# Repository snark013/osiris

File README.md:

# Osiris

65%/75% size (68/78 keys) mechanical keyboard with optional functions keys section.
Osiris can use any supported controller in Pro Micro form factor ([Alvaro](https://github.com/Ariamelon/Alvaro) and [nRFMicro](https://github.com/joric/nrfmicro/wiki) controllers recommended).

Keyboards  photo -

Bluetooth connected (nRFMicro) 78 keys keyboard

USB connected (Pro Micro) 68 keys keyboard with RGB backlight

First prototype (USB connected, Pro Micro) 78 keys keyboard

KiCAD images -

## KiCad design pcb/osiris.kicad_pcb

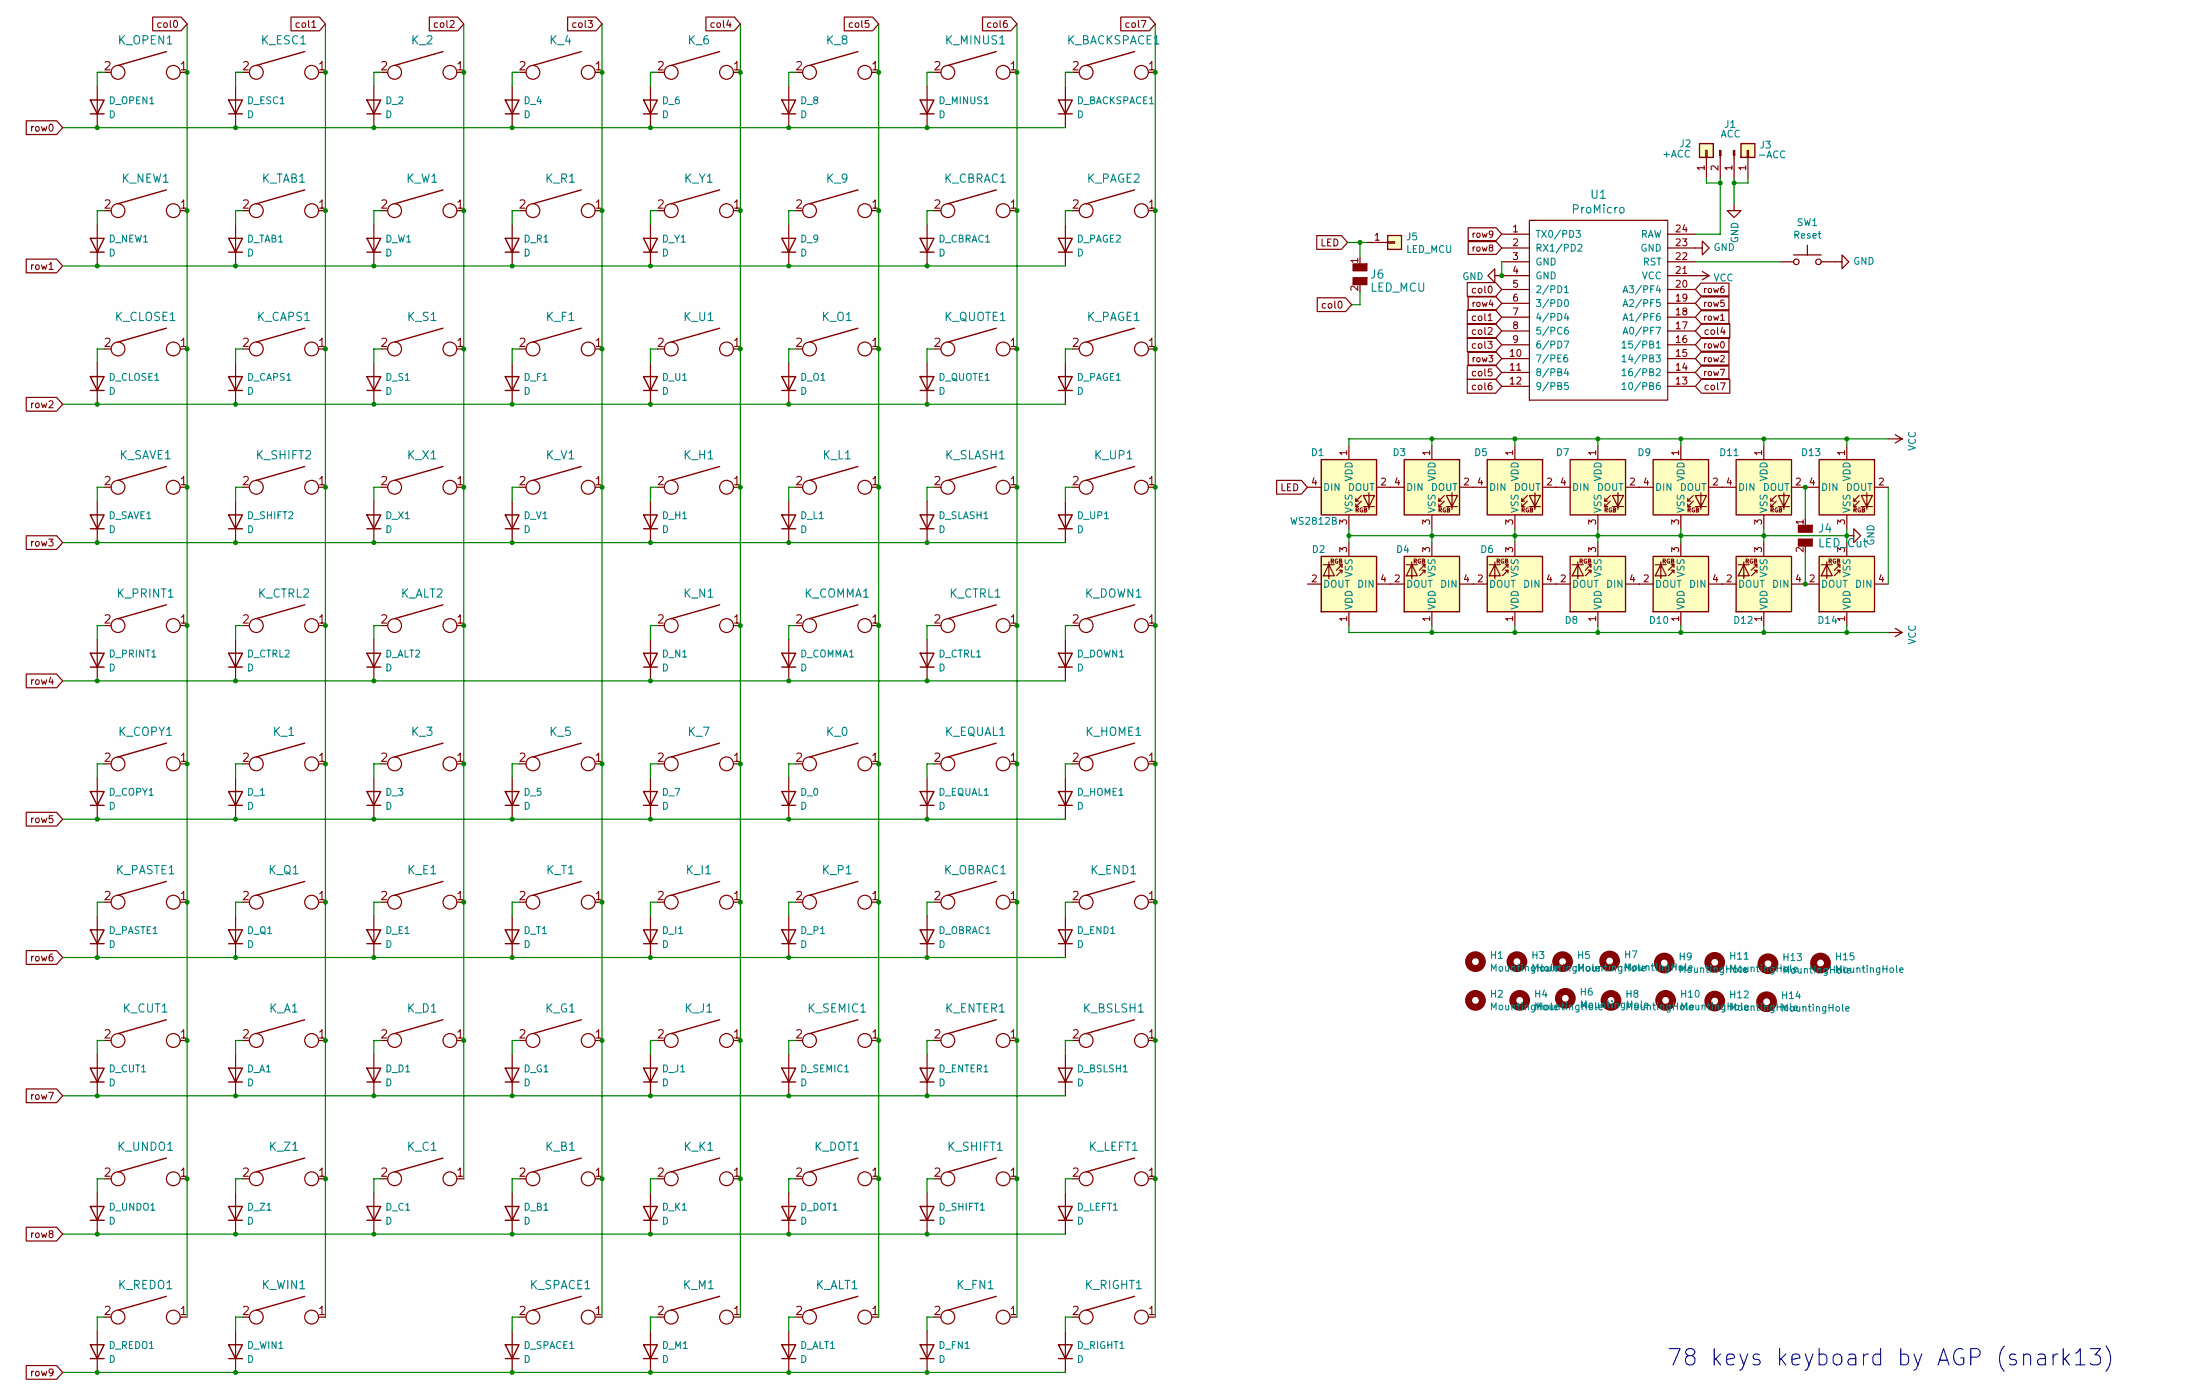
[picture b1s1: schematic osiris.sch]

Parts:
D1, D2, D3, D4, D5, D6, D7, D8, D9, D10, D11, D12, D13, D14: WS2812B; LED_WS2812B_PLCC4_5.0x5.0mm_P3.2mm
D_0, D_1, D_2, D_3, D_4, D_5, D_6, D_7, D_8, D_9: D; D_SOD-323_HandSoldering
D_A1: D; D_SOD-323_HandSoldering
D_ALT1, D_ALT2: D; D_SOD-323_HandSoldering
D_B1: D; D_SOD-323_HandSoldering
D_BACKSPACE1: D; D_SOD-323_HandSoldering
D_BSLSH1: D; D_SOD-323_HandSoldering
D_C1: D; D_SOD-323_HandSoldering
D_CAPS1: D; D_SOD-323_HandSoldering
D_CBRAC1: D; D_SOD-323_HandSoldering
D_CLOSE1: D; D_SOD-323_HandSoldering
D_COMMA1: D; D_SOD-323_HandSoldering
D_COPY1: D; D_SOD-323_HandSoldering
D_CTRL1, D_CTRL2: D; D_SOD-323_HandSoldering
D_CUT1: D; D_SOD-323_HandSoldering
D_D1: D; D_SOD-323_HandSoldering
D_DOT1: D; D_SOD-323_HandSoldering
D_DOWN1: D; D_SOD-323_HandSoldering
D_E1: D; D_SOD-323_HandSoldering
D_END1: D; D_SOD-323_HandSoldering
D_ENTER1: D; D_SOD-323_HandSoldering
D_EQUAL1: D; D_SOD-323_HandSoldering
D_ESC1: D; D_SOD-323_HandSoldering
D_F1: D; D_SOD-323_HandSoldering
D_FN1: D; D_SOD-323_HandSoldering
D_G1: D; D_SOD-323_HandSoldering
D_H1: D; D_SOD-323_HandSoldering
D_HOME1: D; D_SOD-323_HandSoldering
D_I1: D; D_SOD-323_HandSoldering
D_J1: D; D_SOD-323_HandSoldering
D_K1: D; D_SOD-323_HandSoldering
D_L1: D; D_SOD-323_HandSoldering
D_LEFT1: D; D_SOD-323_HandSoldering
D_M1: D; D_SOD-323_HandSoldering
D_MINUS1: D; D_SOD-323_HandSoldering
D_N1: D; D_SOD-323_HandSoldering
D_NEW1: D; D_SOD-323_HandSoldering
D_O1: D; D_SOD-323_HandSoldering
D_OBRAC1: D; D_SOD-323_HandSoldering
D_OPEN1: D; D_SOD-323_HandSoldering
D_P1: D; D_SOD-323_HandSoldering
D_PAGE1, D_PAGE2: D; D_SOD-323_HandSoldering
D_PASTE1: D; D_SOD-323_HandSoldering
D_PRINT1: D; D_SOD-323_HandSoldering
D_Q1: D; D_SOD-323_HandSoldering
D_QUOTE1: D; D_SOD-323_HandSoldering
D_R1: D; D_SOD-323_HandSoldering
D_REDO1: D; D_SOD-323_HandSoldering
D_RIGHT1: D; D_SOD-323_HandSoldering
D_S1: D; D_SOD-323_HandSoldering
D_SAVE1: D; D_SOD-323_HandSoldering
D_SEMIC1: D; D_SOD-323_HandSoldering
D_SHIFT1, D_SHIFT2: D; D_SOD-323_HandSoldering
D_SLASH1: D; D_SOD-323_HandSoldering
D_SPACE1: D; D_SOD-323_HandSoldering
D_T1: D; D_SOD-323_HandSoldering
D_TAB1: D; D_SOD-323_HandSoldering
D_U1: D; D_SOD-323_HandSoldering
D_UNDO1: D; D_SOD-323_HandSoldering
D_UP1: D; D_SOD-323_HandSoldering
D_V1: D; D_SOD-323_HandSoldering
D_W1: D; D_SOD-323_HandSoldering
D_WIN1: D; D_SOD-323_HandSoldering
D_X1: D; D_SOD-323_HandSoldering
D_Y1: D; D_SOD-323_HandSoldering
D_Z1: D; D_SOD-323_HandSoldering
H1, H2, H3, H4, H5, H6, H7, H8, H9, H10, H11, H12, H13, H14, H15: MountingHole; HOLE_M3
J1: ACC; PinSocket_1x02_P2.54mm_Vertical
J2: +ACC; PinSocket_1x01_P2.54mm_Vertical
J3: -ACC; PinSocket_1x01_P2.54mm_Vertical
J4: LED_Cut; Jumper
J5: LED_MCU; Pin_D0.9mm_L10.0mm_W2.4mm_FlatFork
J6: LED_MCU; Jumper
K_0, K_1, K_2, K_3, K_4, K_5, K_6, K_7, K_8, K_9: KEYSW; MXOnly-1U-Hotswap
K_A1: KEYSW; MXOnly-1U-Hotswap
K_ALT1: KEYSW; MXOnly-1.5U-Hotswap
K_ALT2: KEYSW; MXOnly-1.25U-Hotswap
K_B1: KEYSW; MXOnly-1U-Hotswap
K_BACKSPACE1: KEYSW; MXOnly-2U-Hotswap
K_BSLSH1: KEYSW; MXOnly-1.5U-Hotswap
K_C1: KEYSW; MXOnly-1U-Hotswap
K_CAPS1: KEYSW; MXOnly-1.75U-Hotswap
K_CBRAC1: KEYSW; MXOnly-1U-Hotswap
K_CLOSE1: KEYSW; MXOnly-1U-Hotswap
K_COMMA1: KEYSW; MXOnly-1U-Hotswap
K_COPY1: KEYSW; MXOnly-1U-Hotswap
K_CTRL1: KEYSW; MXOnly-1.5U-Hotswap
K_CTRL2: KEYSW; MXOnly-1.25U-Hotswap
K_CUT1: KEYSW; MXOnly-1U-Hotswap
K_D1: KEYSW; MXOnly-1U-Hotswap
K_DOT1: KEYSW; MXOnly-1U-Hotswap
K_DOWN1: KEYSW; MXOnly-1U-Hotswap
K_E1: KEYSW; MXOnly-1U-Hotswap
K_END1: KEYSW; MXOnly-1U-Hotswap
K_ENTER1: KEYSW; MXOnly-2.25U-Hotswap
K_EQUAL1: KEYSW; MXOnly-1U-Hotswap
K_ESC1: KEYSW; MXOnly-1U-Hotswap
K_F1: KEYSW; MXOnly-1U-Hotswap
K_FN1: KEYSW; MXOnly-1U-Hotswap
K_G1: KEYSW; MXOnly-1U-Hotswap
K_H1: KEYSW; MXOnly-1U-Hotswap
K_HOME1: KEYSW; MXOnly-1U-Hotswap
K_I1: KEYSW; MXOnly-1U-Hotswap
K_J1: KEYSW; MXOnly-1U-Hotswap
K_K1: KEYSW; MXOnly-1U-Hotswap
K_L1: KEYSW; MXOnly-1U-Hotswap
K_LEFT1: KEYSW; MXOnly-1U-Hotswap
K_M1: KEYSW; MXOnly-1U-Hotswap
K_MINUS1: KEYSW; MXOnly-1U-Hotswap
K_N1: KEYSW; MXOnly-1U-Hotswap
K_NEW1: KEYSW; MXOnly-1U-Hotswap
K_O1: KEYSW; MXOnly-1U-Hotswap
K_OBRAC1: KEYSW; MXOnly-1U-Hotswap
K_OPEN1: KEYSW; MXOnly-1U-Hotswap
K_P1: KEYSW; MXOnly-1U-Hotswap
K_PAGE1, K_PAGE2: KEYSW; MXOnly-1U-Hotswap
K_PASTE1: KEYSW; MXOnly-1U-Hotswap
K_PRINT1: KEYSW; MXOnly-1U-Hotswap
K_Q1: KEYSW; MXOnly-1U-Hotswap
K_QUOTE1: KEYSW; MXOnly-1U-Hotswap
K_R1: KEYSW; MXOnly-1U-Hotswap
K_REDO1: KEYSW; MXOnly-1U-Hotswap
K_RIGHT1: KEYSW; MXOnly-1U-Hotswap
K_S1: KEYSW; MXOnly-1U-Hotswap
K_SAVE1: KEYSW; MXOnly-1U-Hotswap
K_SEMIC1: KEYSW; MXOnly-1U-Hotswap
K_SHIFT1: KEYSW; MXOnly-2.75U-Hotswap
K_SHIFT2: KEYSW; MXOnly-2.25U-Hotswap
K_SLASH1: KEYSW; MXOnly-1U-Hotswap
K_SPACE1: KEYSW; MXOnly-6.25U-Hotswap-ReversedStabilizers
K_T1: KEYSW; MXOnly-1U-Hotswap
K_TAB1: KEYSW; MXOnly-1.5U-Hotswap
K_U1: KEYSW; MXOnly-1U-Hotswap
K_UNDO1: KEYSW; MXOnly-1U-Hotswap
K_UP1: KEYSW; MXOnly-1U-Hotswap
K_V1: KEYSW; MXOnly-1U-Hotswap
K_W1: KEYSW; MXOnly-1U-Hotswap
K_WIN1: KEYSW; MXOnly-1.25U-Hotswap
K_X1: KEYSW; MXOnly-1U-Hotswap
K_Y1: KEYSW; MXOnly-1U-Hotswap
K_Z1: KEYSW; MXOnly-1U-Hotswap
SW1: Reset; SW_SPST_CK_RS282G05A3
U1: ProMicro; ArduinoProMicro

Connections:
GND: D1.3 (VSS), D2.3 (VSS), D3.3 (VSS), D4.3 (VSS), D5.3 (VSS), D6.3 (VSS), D7.3 (VSS), D8.3 (VSS), D9.3 (VSS), D10.3 (VSS), D11.3 (VSS), D12.3 (VSS), D13.3 (VSS), D14.3 (VSS), J1.1, J3.1, SW1.2, U1.3 (GND), U1.4 (GND), U1.23 (GND)
LED: D1.4 (DIN), J5.1, J6.1
unnamed: D1.2 (DOUT), D3.4 (DIN)
unnamed: D2.4 (DIN), D4.2 (DOUT)
unnamed: D3.2 (DOUT), D5.4 (DIN)
unnamed: D4.4 (DIN), D6.2 (DOUT)
unnamed: D5.2 (DOUT), D7.4 (DIN)
unnamed: D6.4 (DIN), D8.2 (DOUT)
unnamed: D7.2 (DOUT), D9.4 (DIN)
unnamed: D8.4 (DIN), D10.2 (DOUT)
unnamed: D10.4 (DIN), D12.2 (DOUT)
unnamed: D11.2 (DOUT), D13.4 (DIN), J4.1
unnamed: D9.2 (DOUT), D11.4 (DIN)
unnamed: D12.4 (DIN), D14.2 (DOUT), J4.2
unnamed: D13.2 (DOUT), D14.4 (DIN)
unnamed: D_0.2 (A), K_0.2
unnamed: D_1.2 (A), K_1.2
unnamed: D_2.2 (A), K_2.2
unnamed: D_3.2 (A), K_3.2
unnamed: D_4.2 (A), K_4.2
unnamed: D_5.2 (A), K_5.2
unnamed: D_6.2 (A), K_6.2
unnamed: D_7.2 (A), K_7.2
unnamed: D_8.2 (A), K_8.2
unnamed: D_9.2 (A), K_9.2
unnamed: D_A1.2 (A), K_A1.2
unnamed: D_ALT1.2 (A), K_ALT1.2
unnamed: D_ALT2.2 (A), K_ALT2.2
unnamed: D_B1.2 (A), K_B1.2
unnamed: D_BACKSPACE1.2 (A), K_BACKSPACE1.2
unnamed: D_BSLSH1.2 (A), K_BSLSH1.2
unnamed: D_C1.2 (A), K_C1.2
unnamed: D_CAPS1.2 (A), K_CAPS1.2
unnamed: D_CBRAC1.2 (A), K_CBRAC1.2
unnamed: D_CLOSE1.2 (A), K_CLOSE1.2
unnamed: D_COMMA1.2 (A), K_COMMA1.2
unnamed: D_COPY1.2 (A), K_COPY1.2
unnamed: D_CTRL1.2 (A), K_CTRL1.2
unnamed: D_CTRL2.2 (A), K_CTRL2.2
unnamed: D_CUT1.2 (A), K_CUT1.2
unnamed: D_D1.2 (A), K_D1.2
unnamed: D_DOT1.2 (A), K_DOT1.2
unnamed: D_DOWN1.2 (A), K_DOWN1.2
unnamed: D_E1.2 (A), K_E1.2
unnamed: D_END1.2 (A), K_END1.2
unnamed: D_ENTER1.2 (A), K_ENTER1.2
unnamed: D_EQUAL1.2 (A), K_EQUAL1.2
unnamed: D_ESC1.2 (A), K_ESC1.2
unnamed: D_F1.2 (A), K_F1.2
unnamed: D_FN1.2 (A), K_FN1.2
unnamed: D_G1.2 (A), K_G1.2
unnamed: D_H1.2 (A), K_H1.2
unnamed: D_HOME1.2 (A), K_HOME1.2
unnamed: D_I1.2 (A), K_I1.2
unnamed: D_J1.2 (A), K_J1.2
unnamed: D_K1.2 (A), K_K1.2
unnamed: D_L1.2 (A), K_L1.2
unnamed: D_LEFT1.2 (A), K_LEFT1.2
unnamed: D_M1.2 (A), K_M1.2
unnamed: D_MINUS1.2 (A), K_MINUS1.2
unnamed: D_N1.2 (A), K_N1.2
unnamed: D_NEW1.2 (A), K_NEW1.2
unnamed: D_O1.2 (A), K_O1.2
unnamed: D_OBRAC1.2 (A), K_OBRAC1.2
unnamed: D_OPEN1.2 (A), K_OPEN1.2
unnamed: D_P1.2 (A), K_P1.2
unnamed: D_PAGE1.2 (A), K_PAGE1.2
unnamed: D_PAGE2.2 (A), K_PAGE2.2
unnamed: D_PASTE1.2 (A), K_PASTE1.2
unnamed: D_PRINT1.2 (A), K_PRINT1.2
unnamed: D_Q1.2 (A), K_Q1.2
unnamed: D_QUOTE1.2 (A), K_QUOTE1.2
unnamed: D_R1.2 (A), K_R1.2
unnamed: D_REDO1.2 (A), K_REDO1.2
unnamed: D_RIGHT1.2 (A), K_RIGHT1.2
unnamed: D_S1.2 (A), K_S1.2
unnamed: D_SAVE1.2 (A), K_SAVE1.2
unnamed: D_SEMIC1.2 (A), K_SEMIC1.2
unnamed: D_SHIFT1.2 (A), K_SHIFT1.2
unnamed: D_SHIFT2.2 (A), K_SHIFT2.2
unnamed: D_SLASH1.2 (A), K_SLASH1.2
unnamed: D_SPACE1.2 (A), K_SPACE1.2
unnamed: D_T1.2 (A), K_T1.2
unnamed: D_TAB1.2 (A), K_TAB1.2
unnamed: D_U1.2 (A), K_U1.2
unnamed: D_UNDO1.2 (A), K_UNDO1.2
unnamed: D_UP1.2 (A), K_UP1.2
unnamed: D_V1.2 (A), K_V1.2
unnamed: D_W1.2 (A), K_W1.2
unnamed: D_WIN1.2 (A), K_WIN1.2
unnamed: D_X1.2 (A), K_X1.2
unnamed: D_Y1.2 (A), K_Y1.2
unnamed: D_Z1.2 (A), K_Z1.2
unnamed: J1.2, J2.1, U1.24 (RAW)
unnamed: SW1.1, U1.22 (RST)
VCC: D1.1 (VDD), D2.1 (VDD), D3.1 (VDD), D4.1 (VDD), D5.1 (VDD), D6.1 (VDD), D7.1 (VDD), D8.1 (VDD), D9.1 (VDD), D10.1 (VDD), D11.1 (VDD), D12.1 (VDD), D13.1 (VDD), D14.1 (VDD), U1.21 (VCC)
col0: J6.2, K_CLOSE1.1, K_COPY1.1, K_CUT1.1, K_NEW1.1, K_OPEN1.1, K_PASTE1.1, K_PRINT1.1, K_REDO1.1, K_SAVE1.1, K_UNDO1.1, U1.5 (2/PD1)
col1: K_1.1, K_A1.1, K_CAPS1.1, K_CTRL2.1, K_ESC1.1, K_Q1.1, K_SHIFT2.1, K_TAB1.1, K_WIN1.1, K_Z1.1, U1.7 (4/PD4)
col2: K_2.1, K_3.1, K_ALT2.1, K_C1.1, K_D1.1, K_E1.1, K_S1.1, K_W1.1, K_X1.1, U1.8 (5/PC6)
col3: K_4.1, K_5.1, K_B1.1, K_F1.1, K_G1.1, K_R1.1, K_SPACE1.1, K_T1.1, K_V1.1, U1.9 (6/PD7)
col4: K_6.1, K_7.1, K_H1.1, K_I1.1, K_J1.1, K_K1.1, K_M1.1, K_N1.1, K_U1.1, K_Y1.1, U1.17 (A0/PF7)
col5: K_0.1, K_8.1, K_9.1, K_ALT1.1, K_COMMA1.1, K_DOT1.1, K_L1.1, K_O1.1, K_P1.1, K_SEMIC1.1, U1.11 (8/PB4)
col6: K_CBRAC1.1, K_CTRL1.1, K_ENTER1.1, K_EQUAL1.1, K_FN1.1, K_MINUS1.1, K_OBRAC1.1, K_QUOTE1.1, K_SHIFT1.1, K_SLASH1.1, U1.12 (9/PB5)
col7: K_BACKSPACE1.1, K_BSLSH1.1, K_DOWN1.1, K_END1.1, K_HOME1.1, K_LEFT1.1, K_PAGE1.1, K_PAGE2.1, K_RIGHT1.1, K_UP1.1, U1.13 (10/PB6)
row0: D_2.1 (K), D_4.1 (K), D_6.1 (K), D_8.1 (K), D_BACKSPACE1.1 (K), D_ESC1.1 (K), D_MINUS1.1 (K), D_OPEN1.1 (K), U1.16 (15/PB1)
row1: D_9.1 (K), D_CBRAC1.1 (K), D_NEW1.1 (K), D_PAGE2.1 (K), D_R1.1 (K), D_TAB1.1 (K), D_W1.1 (K), D_Y1.1 (K), U1.18 (A1/PF6)
row2: D_CAPS1.1 (K), D_CLOSE1.1 (K), D_F1.1 (K), D_O1.1 (K), D_PAGE1.1 (K), D_QUOTE1.1 (K), D_S1.1 (K), D_U1.1 (K), U1.15 (14/PB3)
row3: D_H1.1 (K), D_L1.1 (K), D_SAVE1.1 (K), D_SHIFT2.1 (K), D_SLASH1.1 (K), D_UP1.1 (K), D_V1.1 (K), D_X1.1 (K), U1.10 (7/PE6)
row4: D_ALT2.1 (K), D_COMMA1.1 (K), D_CTRL1.1 (K), D_CTRL2.1 (K), D_DOWN1.1 (K), D_N1.1 (K), D_PRINT1.1 (K), U1.6 (3/PD0)
row5: D_0.1 (K), D_1.1 (K), D_3.1 (K), D_5.1 (K), D_7.1 (K), D_COPY1.1 (K), D_EQUAL1.1 (K), D_HOME1.1 (K), U1.19 (A2/PF5)
row6: D_E1.1 (K), D_END1.1 (K), D_I1.1 (K), D_OBRAC1.1 (K), D_P1.1 (K), D_PASTE1.1 (K), D_Q1.1 (K), D_T1.1 (K), U1.20 (A3/PF4)
row7: D_A1.1 (K), D_BSLSH1.1 (K), D_CUT1.1 (K), D_D1.1 (K), D_ENTER1.1 (K), D_G1.1 (K), D_J1.1 (K), D_SEMIC1.1 (K), U1.14 (16/PB2)
row8: D_B1.1 (K), D_C1.1 (K), D_DOT1.1 (K), D_K1.1 (K), D_LEFT1.1 (K), D_SHIFT1.1 (K), D_UNDO1.1 (K), D_Z1.1 (K), U1.2 (RX1/PD2)
row9: D_ALT1.1 (K), D_FN1.1 (K), D_M1.1 (K), D_REDO1.1 (K), D_RIGHT1.1 (K), D_SPACE1.1 (K), D_WIN1.1 (K), U1.1 (TX0/PD3)

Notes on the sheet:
78 keys keyboard by AGP (snark13)

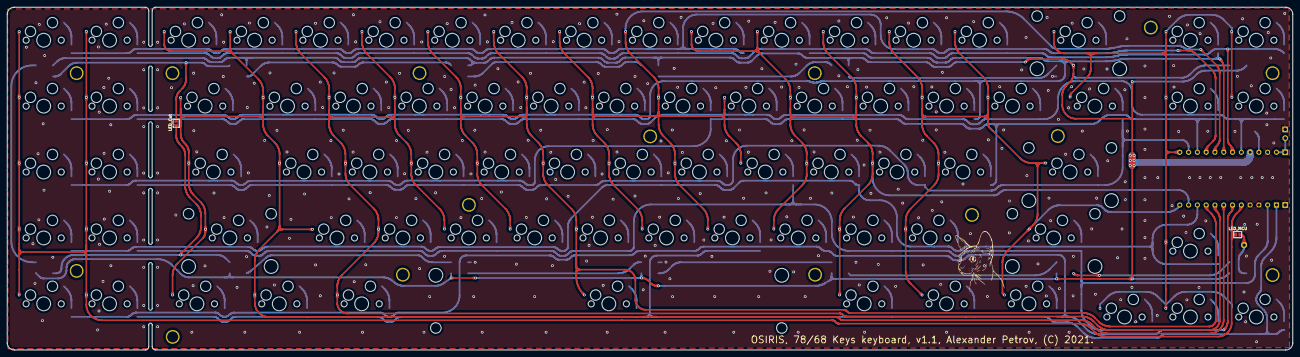
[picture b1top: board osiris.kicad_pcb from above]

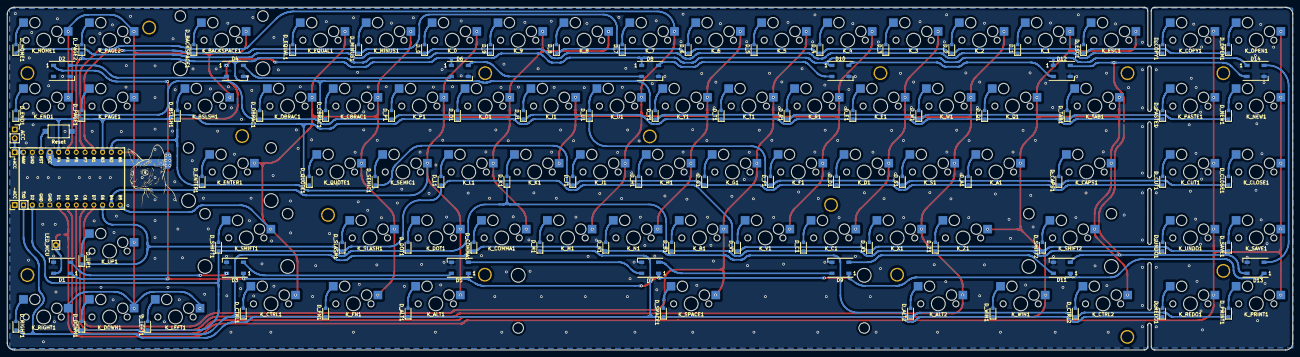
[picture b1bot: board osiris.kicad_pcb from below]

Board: 2 copper layers, 371.6 x 99.1 mm, 193 parts (98 on the bottom side), 114 nets.

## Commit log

2021-08-29 ChangeLog: initial version.
2021-08-29 ChangeLog: photo of keyboard added.
2021-08-29 ChangeLog: - add plate images from Kicad.
2021-08-29 ChangeLog: - 3D print case and top plate added.
2021-08-30 ChangeLog: new photos.
2021-11-01 ChangeLog: - new photo.
2021-11-01 ChangeLog: - photo added.

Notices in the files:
pcb/osiris.kicad_pcb:
OSIRIS, 78/68 Keys keyboard, v1.1, Alexander Petrov, (C) 2021.
